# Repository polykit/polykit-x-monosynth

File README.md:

# Polykit X1 Semi Modular Synthesizer

This repository contains schematics, PCB layout files and front panel for an analog, semi modular, patchable synthesizer. It is an interface that works in conjunction with my voice card https://github.com/polykit/polykit-x-voice-card

Specs of the voice card:

* a VCO with saw, pulse and triangle signal
* an envelope generator
* a multimode filter with 8 different filter responses
* an external input
* and a panning stereo output

See voice card repository for a full feature list.

Specs of the semi modular interface:

* a LFO where the waveform can be blended between triangle and pulse signal
* a wave folder
* a two channel mixer where one input can be attenuated
* an additional attenuator
* a buffered multiple
* different offset voltages
* and a power supply
* 3D printable case

Video playlist on its functionality and design process: https://www.youtube.com/watch?v=2grRbG7IwDw&list=PLUKLEU8jmlbHH4_13YZM0MI6ez4gYQPfy

Gerber files [can be found here](plots/), front panel files are located [here](frontpanel).

## BOM

|Ref                                                                                                                                                      |Qnty|Value              |Name                  |Description                                                             |
|---------------------------------------------------------------------------------------------------------------------------------------------------------|----|-------------------|----------------------|------------------------------------------------------------------------|
|C1, C2                                                                                                                                                   |2   |1000uF             |C_Polarized           |Electrolytic capacitor                                                     |
|C3, C4                                                                                                                                                   |2   |100uF              |C_Polarized           |Electrolytic capacitor                                                     |
|C5, C6                                                                                                                                                   |2   |10uF               |C_Polarized           |Electrolytic capacitor                                                     |
|C7, C8                                                                                                                                                   |2   |1uF                |C_Polarized           |Electrolytic capacitor                                                     |
|C9                                                                                                                                                       |1   |2u2 non-polarized |C                     |Film or ceramic capacitor                                                   |
|C10, C11, C12, C13, C14                                                                                                                                  |5   |100n               |C                     |Ceramic capacitor                                                   |
|D1                                                                                                                                                       |1   |LED                |LED                   |Light emitting diode                                                    |
|D2, D3                                                                                                                                                   |2   |US1G               |US1G                  |400V, 1A, General Purpose Rectifier Diode, SMA(DO-214AC)                |
|D4, D6, D7, D8, D9, D10, D11, D12, D13, D14, D15                                                                                                         |11  |BAS85              |D_Schottky            |Schottky diode                                                          |
|D5                                                                                                                                                       |1   |Dual LED           |LED_Dual_Bidirectional|Dual LED, bidirectional                                                 |
|J1                                                                                                                                                       |1   |OUT LEFT           |AudioJack2_SwitchT    |Audio Jack, 2 Poles (Mono / TS), https://www.thonk.co.uk/shop/thonkiconn|
|J2                                                                                                                                                       |1   |OUT RIGHT          |AudioJack2_SwitchT    |Audio Jack, 2 Poles (Mono / TS), https://www.thonk.co.uk/shop/thonkiconn|
|J3                                                                                                                                                       |1   |ADSR_OUT           |AudioJack2_SwitchT    |Audio Jack, 2 Poles (Mono / TS), https://www.thonk.co.uk/shop/thonkiconn|
|J4                                                                                                                                                       |1   |GATE               |AudioJack2_SwitchT    |Audio Jack, 2 Poles (Mono / TS), https://www.thonk.co.uk/shop/thonkiconn|
|J5                                                                                                                                                       |1   |TRIGGER            |AudioJack2_SwitchT    |Audio Jack, 2 Poles (Mono / TS), https://www.thonk.co.uk/shop/thonkiconn|
|J6                                                                                                                                                       |1   |Conn_01x36         |Conn_01x36            |Pinheader, 01x36                                                        |
|J7                                                                                                                                                       |1   |12V AC             |Jack-DC               |Barrel Jack Socket, 12V AC/AC 1A wall wart power supply is needed              |
|J8                                                                                                                                                       |1   |LFO                |AudioJack2_SwitchT    |Audio Jack, 2 Poles (Mono / TS), https://www.thonk.co.uk/shop/thonkiconn|
|J9                                                                                                                                                       |1   |PAN_CV             |AudioJack2_SwitchT    |Audio Jack, 2 Poles (Mono / TS), https://www.thonk.co.uk/shop/thonkiconn|
|J10                                                                                                                                                      |1   |PWM CV             |AudioJack2_SwitchT    |Audio Jack, 2 Poles (Mono / TS), https://www.thonk.co.uk/shop/thonkiconn|
|J11                                                                                                                                                      |1   |RES CV             |AudioJack2_SwitchT    |Audio Jack, 2 Poles (Mono / TS), https://www.thonk.co.uk/shop/thonkiconn|
|J12                                                                                                                                                      |1   |FREQ CV            |AudioJack2_SwitchT    |Audio Jack, 2 Poles (Mono / TS), https://www.thonk.co.uk/shop/thonkiconn|
|J13                                                                                                                                                      |1   |PITCH CV 1V/OCT    |AudioJack2_SwitchT    |Audio Jack, 2 Poles (Mono / TS), https://www.thonk.co.uk/shop/thonkiconn|
|J14                                                                                                                                                      |1   |EXT IN             |AudioJack2_SwitchT    |Audio Jack, 2 Poles (Mono / TS), https://www.thonk.co.uk/shop/thonkiconn|
|J15                                                                                                                                                      |1   |VCA CV             |AudioJack2_SwitchT    |Audio Jack, 2 Poles (Mono / TS), https://www.thonk.co.uk/shop/thonkiconn|
|J16                                                                                                                                                      |1   |HARD SYNC          |AudioJack2_SwitchT    |Audio Jack, 2 Poles (Mono / TS), https://www.thonk.co.uk/shop/thonkiconn|
|J17                                                                                                                                                      |1   |SOFT SYNC          |AudioJack2_SwitchT    |Audio Jack, 2 Poles (Mono / TS), https://www.thonk.co.uk/shop/thonkiconn|
|J18                                                                                                                                                      |1   |FM                 |AudioJack2_SwitchT    |Audio Jack, 2 Poles (Mono / TS), https://www.thonk.co.uk/shop/thonkiconn|
|J19                                                                                                                                                      |1   |MULT               |AudioJack2_SwitchT    |Audio Jack, 2 Poles (Mono / TS), https://www.thonk.co.uk/shop/thonkiconn|
|J20                                                                                                                                                      |1   |WAVE IN            |AudioJack2_SwitchT    |Audio Jack, 2 Poles (Mono / TS), https://www.thonk.co.uk/shop/thonkiconn|
|J21                                                                                                                                                      |1   |ATT IN (+5V)       |AudioJack2_SwitchT    |Audio Jack, 2 Poles (Mono / TS), https://www.thonk.co.uk/shop/thonkiconn|
|J22                                                                                                                                                      |1   |MULT1              |AudioJack2_SwitchT    |Audio Jack, 2 Poles (Mono / TS), https://www.thonk.co.uk/shop/thonkiconn|
|J23                                                                                                                                                      |1   |MULT2              |AudioJack2_SwitchT    |Audio Jack, 2 Poles (Mono / TS), https://www.thonk.co.uk/shop/thonkiconn|
|J24                                                                                                                                                      |1   |ATT OUT            |AudioJack2_SwitchT    |Audio Jack, 2 Poles (Mono / TS), https://www.thonk.co.uk/shop/thonkiconn|
|J25                                                                                                                                                      |1   |MIX IN2            |                      |Can be used as default input for MIX2 when not patched                  |
|J26                                                                                                                                                      |1   |MIX IN1 (-5V)      |AudioJack2_SwitchT    |Audio Jack, 2 Poles (Mono / TS), https://www.thonk.co.uk/shop/thonkiconn|
|J27                                                                                                                                                      |1   |MIX IN2            |AudioJack2_SwitchT    |Audio Jack, 2 Poles (Mono / TS), https://www.thonk.co.uk/shop/thonkiconn|
|J28                                                                                                                                                      |1   |WAVE OUT           |AudioJack2_SwitchT    |Audio Jack, 2 Poles (Mono / TS), https://www.thonk.co.uk/shop/thonkiconn|
|J29                                                                                                                                                      |1   |MIX OUT            |AudioJack2_SwitchT    |Audio Jack, 2 Poles (Mono / TS), https://www.thonk.co.uk/shop/thonkiconn|
|Q1, Q3                                                                                                                                                   |2   |BC847              |BC847                 |0.1A Ic, 45V Vce, NPN Transistor, SOT-23                                |
|Q2                                                                                                                                                       |1   |BC857              |BC857                 |0.1A Ic, 45V Vce, PNP Transistor, SOT-23                                |
|R1, R18, R19, R47, R50                                                                                                                                   |5   |10k                |R                     |Resistor                                                                |
|R2, R3, R4, R5, R20, R21, R45, R46, R54, R58                                                                                                             |10  |1k                 |R                     |Resistor                                                                |
|R10                                                                                                                                                      |1   |100                |R                     |Resistor                                                                |
|R11, R12, R13, R15, R22, R23, R24, R25, R27, R28, R29, R30, R31, R32, R33, R34, R35, R36, R37, R38, R39, R40, R41, R43, R44, R51, R52, R53, R55, R56, R57|31  |100k               |R                     |Resistor                                                                |
|R14                                                                                                                                                      |1   |220k               |R                     |Resistor                                                                |
|R16                                                                                                                                                      |1   |15k                |R                     |Resistor                                                                |
|R17, R48, R49                                                                                                                                            |3   |12k                |R                     |Resistor                                                                |
|R26                                                                                                                                                      |1   |47k                |R                     |Resistor                                                                |
|R42                                                                                                                                                      |1   |470k               |R                     |Resistor                                                                |
|RV1                                                                                                                                                      |1   |B100k LEVEL1       |R_POT-Device          |Potentiometer RK097 Vertical                                            |
|RV2                                                                                                                                                      |1   |B100k LEVEL2       |R_POT-Device          |Potentiometer RK097 Vertical                                            |
|RV3                                                                                                                                                      |1   |10k LFO TRIM       |R_Potentiometer_Trim  |Trim-potentiometer                                                      |
|RV4                                                                                                                                                      |1   |B1M LFO RATE       |R_POT-Device          |Potentiometer RK097 Vertical                                            |
|RV5                                                                                                                                                      |1   |B100k LFO WAVE     |R_POT-Device          |Potentiometer RK097 Vertical                                            |
|RV6                                                                                                                                                      |1   |B100k PANNING      |R_POT-Device          |Potentiometer RK097 Vertical                                            |
|RV7                                                                                                                                                      |1   |B100k A            |R_POT-Device          |Potentiometer RK097 Vertical                                            |
|RV8                                                                                                                                                      |1   |B100k D            |R_POT-Device          |Potentiometer RK097 Vertical                                            |
|RV9                                                                                                                                                      |1   |B100k S            |R_POT-Device          |Potentiometer RK097 Vertical                                            |
|RV10                                                                                                                                                     |1   |B100k R            |R_POT-Device          |Potentiometer RK097 Vertical                                            |
|RV11                                                                                                                                                     |1   |B100k RES          |R_POT-Device          |Potentiometer RK097 Vertical                                            |
|RV12                                                                                                                                                     |1   |B100k FREQ         |R_POT-Device          |Potentiometer RK097 Vertical                                            |
|RV13                                                                                                                                                     |1   |B100k PWM          |R_POT-Device          |Potentiometer RK097 Vertical                                            |
|RV14                                                                                                                                                     |1   |B100k TUNE         |R_POT-Device          |Potentiometer RK097 Vertical                                            |
|RV15                                                                                                                                                     |1   |B100k ATT          |R_POT-Device          |Potentiometer RK097 Vertical                                            |
|RV16                                                                                                                                                     |1   |B100k MIX IN1 LEVEL|R_POT-Device          |Potentiometer RK097 Vertical                                            |
|SW1                                                                                                                                                      |1   |EXT_ON             |SW_SPDT               |Switch, single pole double throw                                        |
|SW2                                                                                                                                                      |1   |FILTER_A           |SW_SPDT               |Switch, single pole double throw                                        |
|SW3                                                                                                                                                      |1   |FILTER_B           |SW_SPDT               |Switch, single pole double throw                                        |
|SW4                                                                                                                                                      |1   |FILTER_C           |SW_SPDT               |Switch, single pole double throw                                        |
|SW5                                                                                                                                                      |1   |RES_MODE           |SW_SPDT_MSM           |Switch, single pole double throw, center OFF position                   |
|SW6                                                                                                                                                      |1   |FREQ_MODE          |SW_SPDT_MSM           |Switch, single pole double throw, center OFF position                   |
|SW7                                                                                                                                                      |1   |SAW_TRIANGLE       |SW_SPDT               |Switch, single pole double throw                                        |
|U1                                                                                                                                                       |1   |MC78M12_TO252      |78M12 TO-252          |Positive 500mA 35V Linear Regulator, Fixed Output 5V, TO-252 (D-PAK)    |
|U2                                                                                                                                                       |1   |MC79M12_TO252      |79M12 TO-252          |Negative 500mA 35V Linear Regulator, Fixed Output -12V, TO-252 (D-PAK)  |
|U3                                                                                                                                                       |1   |L78L05_SO8         |78L05 SO-8            |Positive 100mA 30V Linear Regulator, Fixed Output 5V, SO-8              |
|U4                                                                                                                                                       |1   |L79L05_SO8         |79L05 SO-8            |Negative 100mA -30V Linear Regulator, Fixed Output -5V, SO-8            |
|U5, U6, U7, U8                                                                                                                                           |4   |TL074              |TL074                 |Quad Low-Noise JFET-Input Operational Amplifiers, DIP-14/SOIC-14        |
|U9                                                                                                                                                       |1   |TL072              |TL072                 |Dual Low-Noise JFET-Input Operational Amplifiers, DIP-8/SOIC-8          |

## Tuning

See voice card repository for details on tuning. Additional male/female dupont cables are needed in order to get access to the trimpots. Minimal set of connections are ground, all four voltages, PITCH, PWM, ADSR_*, GATE, LVL2, FREQ_CV and outputs.

## Modifications

`SAW` output of the oscillator can be added to `MIX IN2` default input via a 1k resistor, eg. by tapping into the signal between `R1` and `U6` pin 8 on the voice card.

## References

Voice Card: https://github.com/polykit/polykit-x-voice-card

Footprints: https://github.com/polykit/kicad

Wavefolder: https://www.elby-designs.com/webtek/cgs/cgs52/cgs52_folder.html

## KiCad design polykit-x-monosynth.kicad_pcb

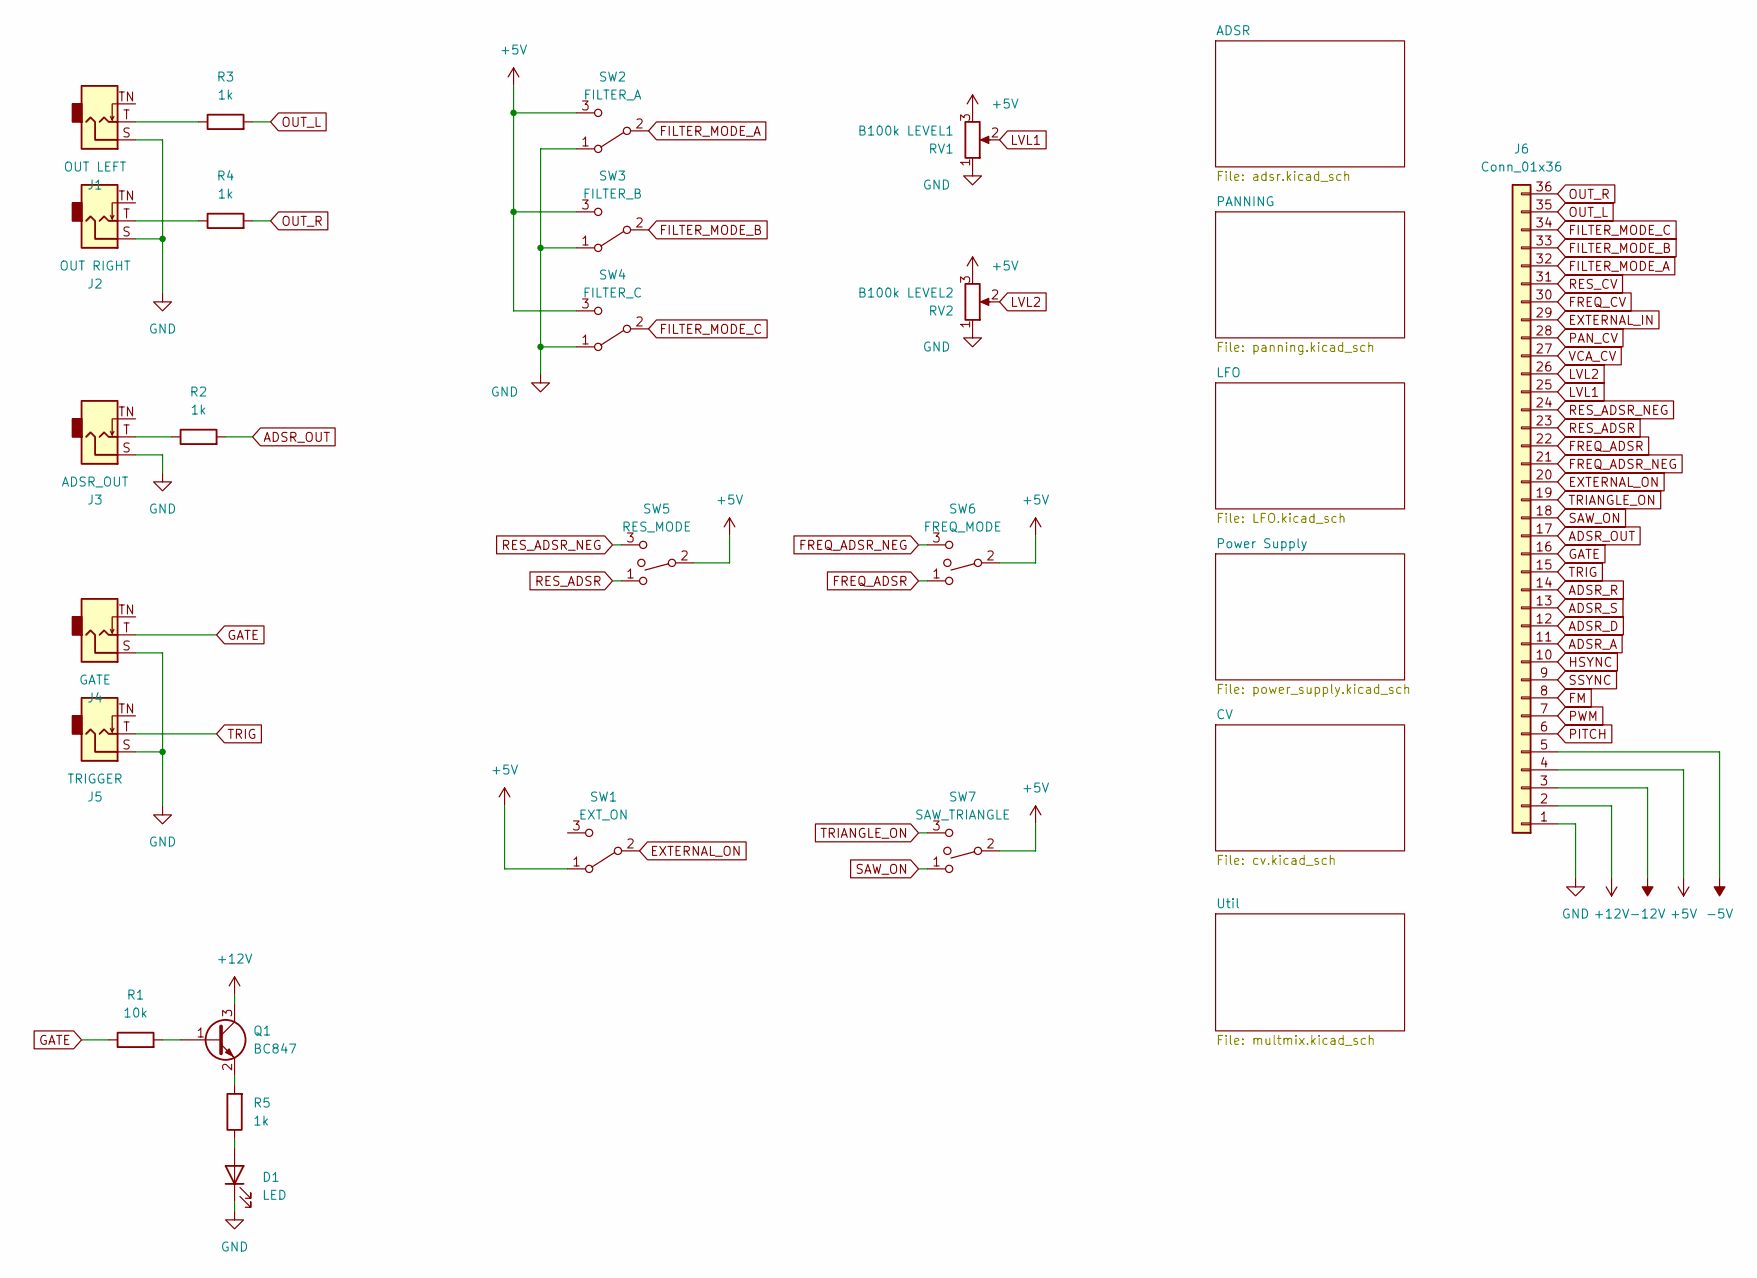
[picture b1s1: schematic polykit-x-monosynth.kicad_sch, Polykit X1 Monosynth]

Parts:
D1: LED; LED_D5.0mm
J1: OUT LEFT; Jack_3.5mm_QingPu_WQP-PJ398SM_Vertical_CircularHoles
J2: OUT RIGHT; Jack_3.5mm_QingPu_WQP-PJ398SM_Vertical_CircularHoles
J3: ADSR_OUT; Jack_3.5mm_QingPu_WQP-PJ398SM_Vertical_CircularHoles
J4: GATE; Jack_3.5mm_QingPu_WQP-PJ398SM_Vertical_CircularHoles
J5: TRIGGER; Jack_3.5mm_QingPu_WQP-PJ398SM_Vertical_CircularHoles
J6: Conn_01x36; PinSocket_1x36_P2.54mm_Vertical
Q1: BC847; SOT-23; LCSC C8659
R1: 10k; R_1206_3216Metric_Pad1.30x1.75mm_HandSolder; LCSC C17902
R2, R3, R4, R5: 1k; R_1206_3216Metric_Pad1.30x1.75mm_HandSolder; LCSC C4410
RV1: B100k LEVEL1; Potentiometer_Alpha_RD901F-40-00D_Single_Vertical_CircularH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
RV2: B100k LEVEL2; Potentiometer_Alpha_RD901F-40-00D_Single_Vertical_CircularH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
SW1: EXT_ON; switch-spdt
SW2: FILTER_A; switch-spdt
SW3: FILTER_B; switch-spdt
SW4: FILTER_C; switch-spdt
SW5: RES_MODE; switch-spdt
SW6: FREQ_MODE; switch-spdt
SW7: SAW_TRIANGLE; switch-spdt

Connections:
+5V: J6.4, RV1.3, RV2.3, SW1.1 (A), SW2.3 (C), SW3.3 (C), SW4.3 (C), SW5.2, SW6.2, SW7.2; also elsewhere on the board
+12V: J6.2, Q1.3 (C); also elsewhere on the board
-5V: J6.5; also elsewhere on the board
-12V: J6.3; also elsewhere on the board
ADSR_A: J6.11; also elsewhere on the board
ADSR_D: J6.12; also elsewhere on the board
ADSR_OUT: J6.17, R2.2; also elsewhere on the board
ADSR_R: J6.14; also elsewhere on the board
ADSR_S: J6.13; also elsewhere on the board
EXTERNAL_IN: J6.29; also elsewhere on the board
EXTERNAL_ON: J6.20, SW1.2 (B)
FILTER_MODE_A: J6.32, SW2.2 (B)
FILTER_MODE_B: J6.33, SW3.2 (B)
FILTER_MODE_C: J6.34, SW4.2 (B)
FM: J6.8; also elsewhere on the board
FREQ_ADSR: J6.22, SW6.1
FREQ_ADSR_NEG: J6.21, SW6.3
FREQ_CV: J6.30; also elsewhere on the board
GATE: J4.T, J6.16, R1.1
HSYNC: J6.10; also elsewhere on the board
LVL1: J6.25, RV1.2
LVL2: J6.26, RV2.2
unnamed: D1.2 (A), R5.1
unnamed: J1.T, R3.1
unnamed: J2.T, R4.1
unnamed: J3.T, R2.1
unnamed: Q1.1 (B), R1.2
unnamed: Q1.2 (E), R5.2
OUT_L: J6.35, R3.2
OUT_R: J6.36, R4.2
PAN_CV: J6.28; also elsewhere on the board
PITCH: J6.6; also elsewhere on the board
PWM: J6.7; also elsewhere on the board
RES_ADSR: J6.23, SW5.1
RES_ADSR_NEG: J6.24, SW5.3
RES_CV: J6.31; also elsewhere on the board
SAW_ON: J6.18, SW7.1
SSYNC: J6.9; also elsewhere on the board
TRIANGLE_ON: J6.19, SW7.3
TRIG: J5.T, J6.15
VCA_CV: J6.27; also elsewhere on the board

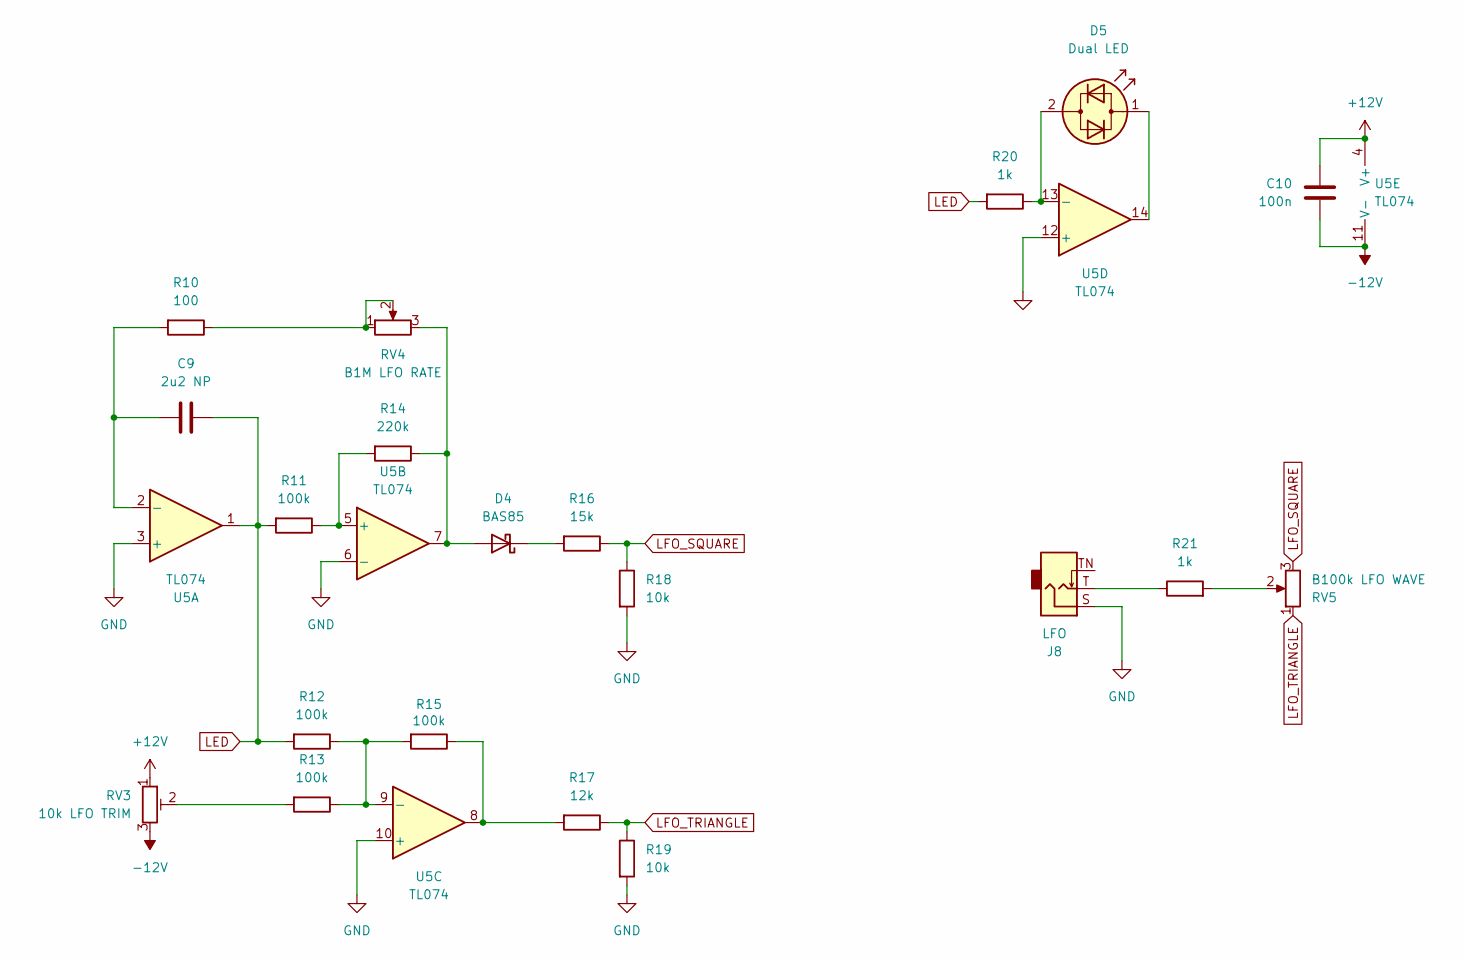
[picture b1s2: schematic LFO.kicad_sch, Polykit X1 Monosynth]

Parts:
C9: 2u2 NP; C_1206_3216Metric_Pad1.33x1.80mm_HandSolder; LCSC C134236
C10: 100n; C_1206_3216Metric_Pad1.33x1.80mm_HandSolder; LCSC C24497
D4: BAS85; D_MiniMELF; LCSC C46677
D5: Dual LED; LED_D5.0mm
J8: LFO; Jack_3.5mm_QingPu_WQP-PJ398SM_Vertical_CircularHoles
R10: 100; R_1206_3216Metric_Pad1.30x1.75mm_HandSolder; LCSC C17901
R11, R12, R13, R15: 100k; R_1206_3216Metric_Pad1.30x1.75mm_HandSolder; LCSC C17900
R14: 220k; R_1206_3216Metric_Pad1.30x1.75mm_HandSolder; LCSC C17956
R16: 15k; R_1206_3216Metric_Pad1.30x1.75mm_HandSolder; LCSC C17912
R17: 12k; R_1206_3216Metric_Pad1.30x1.75mm_HandSolder; LCSC C17912
R18, R19: 10k; R_1206_3216Metric_Pad1.30x1.75mm_HandSolder; LCSC C17902
R20, R21: 1k; R_1206_3216Metric_Pad1.30x1.75mm_HandSolder; LCSC C4410
RV3: 10k LFO TRIM; Potentiometer_Bourns_3314J_Vertical; LCSC C36376
RV4: B1M LFO RATE; Potentiometer_Alpha_RD901F-40-00D_Single_Vertical_CircularH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
RV5: B100k LFO WAVE; Potentiometer_Alpha_RD901F-40-00D_Single_Vertical_CircularH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
U5: TL074; SO-14_3.9x8.65mm_P1.27mm; LCSC C6963

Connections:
+12V: C10.1, RV3.1, U5.4 (V+); also elsewhere on the board
-12V: C10.2, RV3.3, U5.11 (V-); also elsewhere on the board
LED: C9.1, R11.2, R12.2, R20.2, U5.1
LFO_SQUARE: R16.1, R18.1, RV5.3
LFO_TRIANGLE: R17.1, R19.1, RV5.1
unnamed: C9.2, R10.2, U5.2 (-)
unnamed: D4.1 (K), R16.2
unnamed: D4.2 (A), R14.1, RV4.3, U5.7
unnamed: D5.1 (KA), U5.14
unnamed: D5.2 (AK), R20.1, U5.13 (-)
unnamed: J8.T, R21.1
unnamed: R10.1, RV4.1, RV4.2
unnamed: R11.1, R14.2, U5.5 (+)
unnamed: R12.1, R13.1, R15.2, U5.9 (-)
unnamed: R13.2, RV3.2
unnamed: R15.1, R17.2, U5.8
unnamed: R21.2, RV5.2

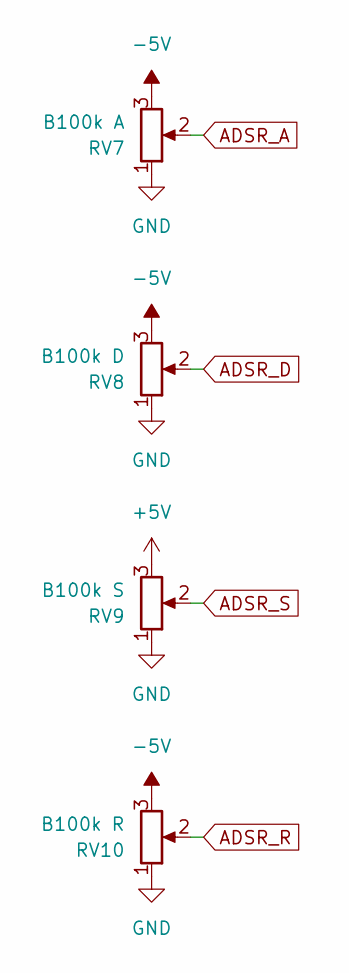
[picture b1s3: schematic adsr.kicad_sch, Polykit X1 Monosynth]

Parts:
RV7: B100k A; Potentiometer_Alpha_RD901F-40-00D_Single_Vertical_CircularH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
RV8: B100k D; Potentiometer_Alpha_RD901F-40-00D_Single_Vertical_CircularH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
RV9: B100k S; Potentiometer_Alpha_RD901F-40-00D_Single_Vertical_CircularH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
RV10: B100k R; Potentiometer_Alpha_RD901F-40-00D_Single_Vertical_CircularH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

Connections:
+5V: RV9.3; also elsewhere on the board
-5V: RV7.3, RV8.3, RV10.3; also elsewhere on the board
ADSR_A: RV7.2; also elsewhere on the board
ADSR_D: RV8.2; also elsewhere on the board
ADSR_R: RV10.2; also elsewhere on the board
ADSR_S: RV9.2; also elsewhere on the board

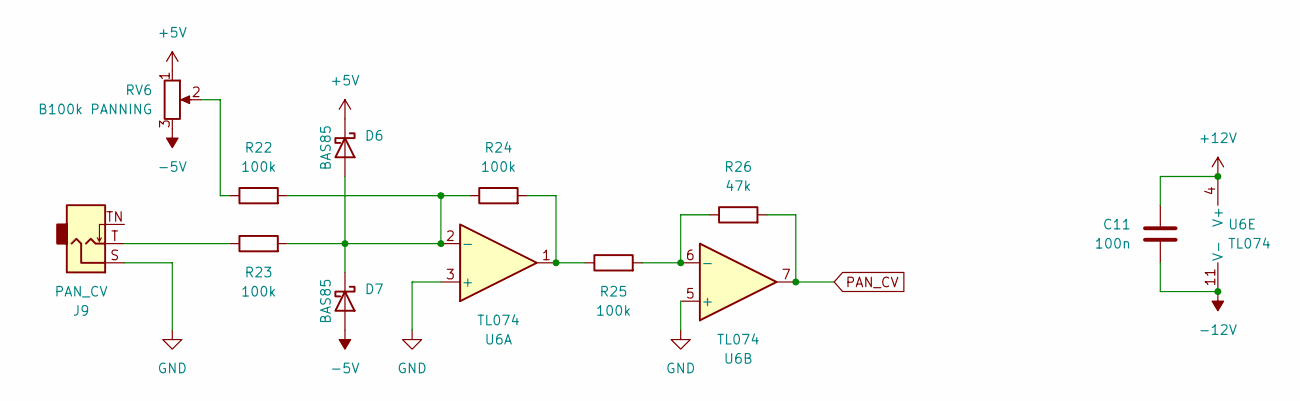
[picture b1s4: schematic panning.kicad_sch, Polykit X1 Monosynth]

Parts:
C11: 100n; C_1206_3216Metric_Pad1.33x1.80mm_HandSolder; LCSC C24497
D6, D7: BAS85; D_MiniMELF; LCSC C46677
J9: PAN_CV; Jack_3.5mm_QingPu_WQP-PJ398SM_Vertical_CircularHoles
R22, R23, R24, R25: 100k; R_1206_3216Metric_Pad1.30x1.75mm_HandSolder; LCSC C17900
R26: 47k; R_1206_3216Metric_Pad1.30x1.75mm_HandSolder; LCSC C25833
RV6: B100k PANNING; Potentiometer_Alpha_RD901F-40-00D_Single_Vertical_CircularH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
U6: TL074; SO-14_3.9x8.65mm_P1.27mm; LCSC C6963

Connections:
+5V: D6.1 (K), RV6.1; also elsewhere on the board
+12V: C11.1, U6.4 (V+); also elsewhere on the board
-5V: D7.2 (A), RV6.3; also elsewhere on the board
-12V: C11.2, U6.11 (V-); also elsewhere on the board
unnamed: D6.2 (A), D7.1 (K), R22.2, R23.2, R24.1, U6.2 (-)
unnamed: J9.T, R23.1
unnamed: R22.1, RV6.2
unnamed: R24.2, R25.1, U6.1
unnamed: R25.2, R26.1, U6.6 (-)
PAN_CV: R26.2, U6.7; also elsewhere on the board

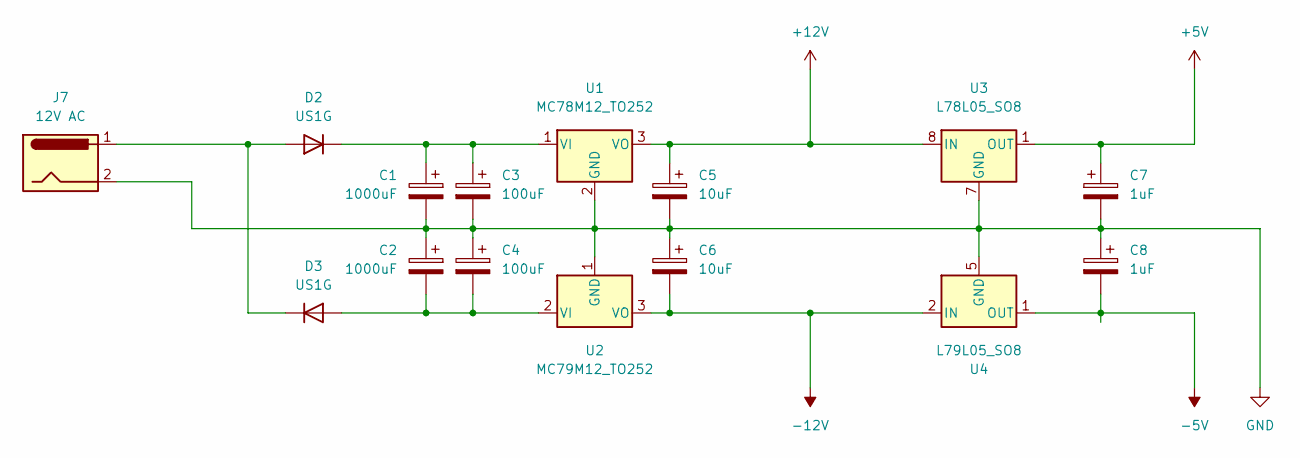
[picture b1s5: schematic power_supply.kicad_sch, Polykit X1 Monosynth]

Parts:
C1, C2: 1000uF; CP_Elec_10x10; LCSC C2904877*
C3, C4: 100uF; CP_Elec_6.3x7.7; LCSC C125975
C5, C6: 10uF; CP_Elec_4x5.8; LCSC C134237*
C7, C8: 1uF; CP_Elec_4x5.4; LCSC C445065
D2, D3: US1G; D_SMA
J7: 12V AC; BarrelJack_Horizontal
U1: MC78M12_TO252; TO-252-2; LCSC C67851
U2: MC79M12_TO252; TO-252-2; LCSC C154823
U3: L78L05_SO8; SOIC-8_3.9x4.9mm_P1.27mm; LCSC C7372
U4: L79L05_SO8; SOIC-8_3.9x4.9mm_P1.27mm; LCSC C222122

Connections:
+5V: C7.1, U3.1 (OUT); also elsewhere on the board
+12V: C5.1, U1.3 (VO), U3.8 (IN); also elsewhere on the board
-5V: C8.2, U4.1 (OUT); also elsewhere on the board
-12V: C6.2, U2.3 (VO), U4.2 (IN), U4.3 (IN), U4.6 (IN), U4.7 (IN); also elsewhere on the board
unnamed: C1.1, C3.1, D2.1 (K), U1.1 (VI)
unnamed: C2.2, C4.2, D3.2 (A), U2.2 (VI)
unnamed: D2.2 (A), D3.1 (K), J7.1

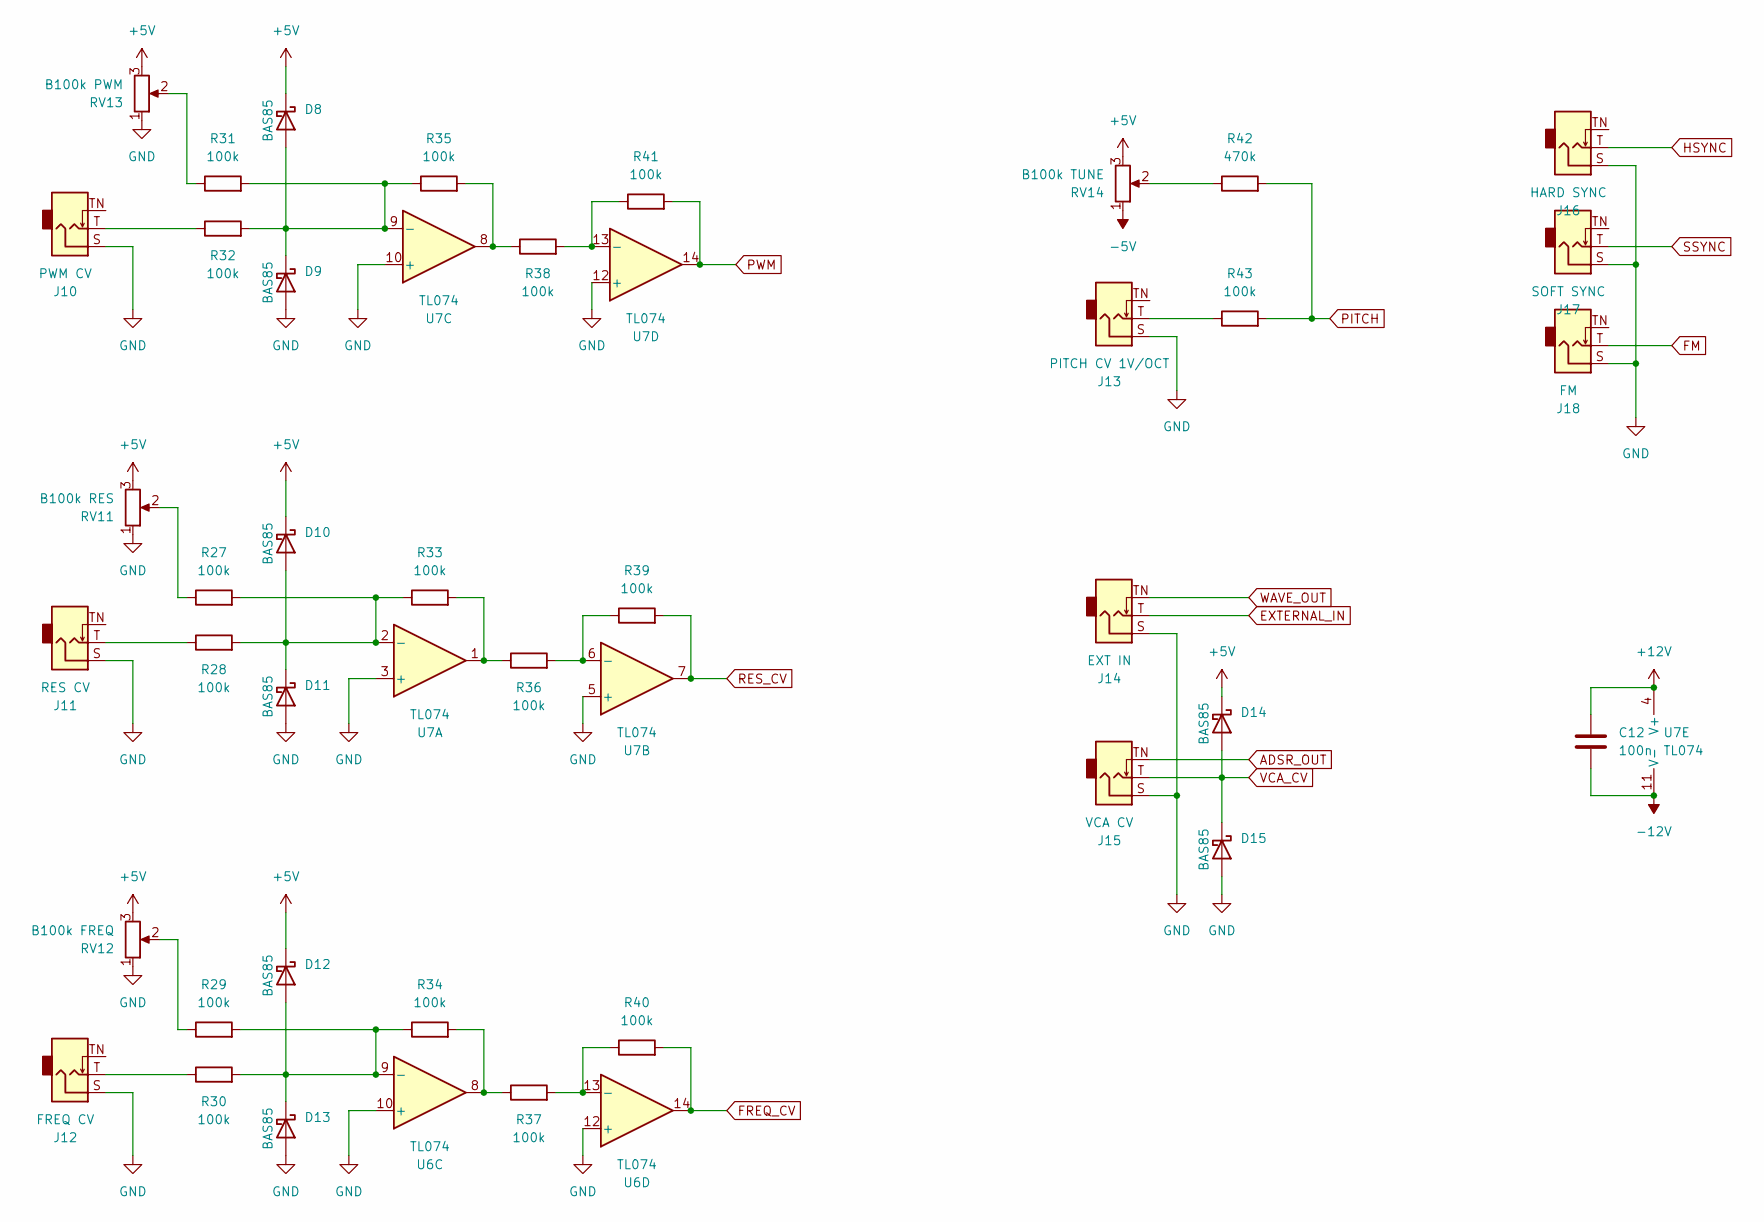
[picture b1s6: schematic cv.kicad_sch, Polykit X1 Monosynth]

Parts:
C12: 100n; C_1206_3216Metric_Pad1.33x1.80mm_HandSolder; LCSC C24497
D8, D9, D10, D11, D12, D13, D14, D15: BAS85; D_MiniMELF; LCSC C46677
J10: PWM CV; Jack_3.5mm_QingPu_WQP-PJ398SM_Vertical_CircularHoles
J11: RES CV; Jack_3.5mm_QingPu_WQP-PJ398SM_Vertical_CircularHoles
J12: FREQ CV; Jack_3.5mm_QingPu_WQP-PJ398SM_Vertical_CircularHoles
J13: PITCH CV 1V/OCT; Jack_3.5mm_QingPu_WQP-PJ398SM_Vertical_CircularHoles
J14: EXT IN; Jack_3.5mm_QingPu_WQP-PJ398SM_Vertical_CircularHoles
J15: VCA CV; Jack_3.5mm_QingPu_WQP-PJ398SM_Vertical_CircularHoles
J16: HARD SYNC; Jack_3.5mm_QingPu_WQP-PJ398SM_Vertical_CircularHoles
J17: SOFT SYNC; Jack_3.5mm_QingPu_WQP-PJ398SM_Vertical_CircularHoles
J18: FM; Jack_3.5mm_QingPu_WQP-PJ398SM_Vertical_CircularHoles
R27, R28, R29, R30, R31, R32, R33, R34, R35, R36, R37, R38, R39, R40, R41, R43: 100k; R_1206_3216Metric_Pad1.30x1.75mm_HandSolder; LCSC C17900
R42: 470k; R_1206_3216Metric_Pad1.30x1.75mm_HandSolder; LCSC C25663
RV11: B100k RES; Potentiometer_Alpha_RD901F-40-00D_Single_Vertical_CircularH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
RV12: B100k FREQ; Potentiometer_Alpha_RD901F-40-00D_Single_Vertical_CircularH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
RV13: B100k PWM; Potentiometer_Alpha_RD901F-40-00D_Single_Vertical_CircularH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
RV14: B100k TUNE; Potentiometer_Alpha_RD901F-40-00D_Single_Vertical_CircularH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
U6, U7: TL074; SO-14_3.9x8.65mm_P1.27mm; LCSC C6963

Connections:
+5V: D8.1 (K), D10.1 (K), D12.1 (K), D14.1 (K), RV11.3, RV12.3, RV13.3, RV14.3; also elsewhere on the board
+12V: C12.1, U7.4 (V+); also elsewhere on the board
-5V: RV14.1; also elsewhere on the board
-12V: C12.2, U7.11 (V-); also elsewhere on the board
ADSR_OUT: J15.TN; also elsewhere on the board
EXTERNAL_IN: J14.T; also elsewhere on the board
FM: J18.T; also elsewhere on the board
FREQ_CV: R40.2, U6.14; also elsewhere on the board
HSYNC: J16.T; also elsewhere on the board
unnamed: D8.2 (A), D9.1 (K), R31.2, R32.2, R35.1, U7.9 (-)
unnamed: D10.2 (A), D11.1 (K), R27.2, R28.2, R33.1, U7.2 (-)
unnamed: D12.2 (A), D13.1 (K), R29.2, R30.2, R34.1, U6.9 (-)
unnamed: J10.T, R32.1
unnamed: J11.T, R28.1
unnamed: J12.T, R30.1
unnamed: J13.T, R43.1
unnamed: R27.1, RV11.2
unnamed: R29.1, RV12.2
unnamed: R31.1, RV13.2
unnamed: R33.2, R36.1, U7.1
unnamed: R34.2, R37.1, U6.8
unnamed: R35.2, R38.1, U7.8
unnamed: R36.2, R39.1, U7.6 (-)
unnamed: R37.2, R40.1, U6.13 (-)
unnamed: R38.2, R41.1, U7.13 (-)
unnamed: R42.1, RV14.2
PITCH: R42.2, R43.2; also elsewhere on the board
PWM: R41.2, U7.14; also elsewhere on the board
RES_CV: R39.2, U7.7; also elsewhere on the board
SSYNC: J17.T; also elsewhere on the board
VCA_CV: D14.2 (A), D15.1 (K), J15.T; also elsewhere on the board
WAVE_OUT: J14.TN; also elsewhere on the board

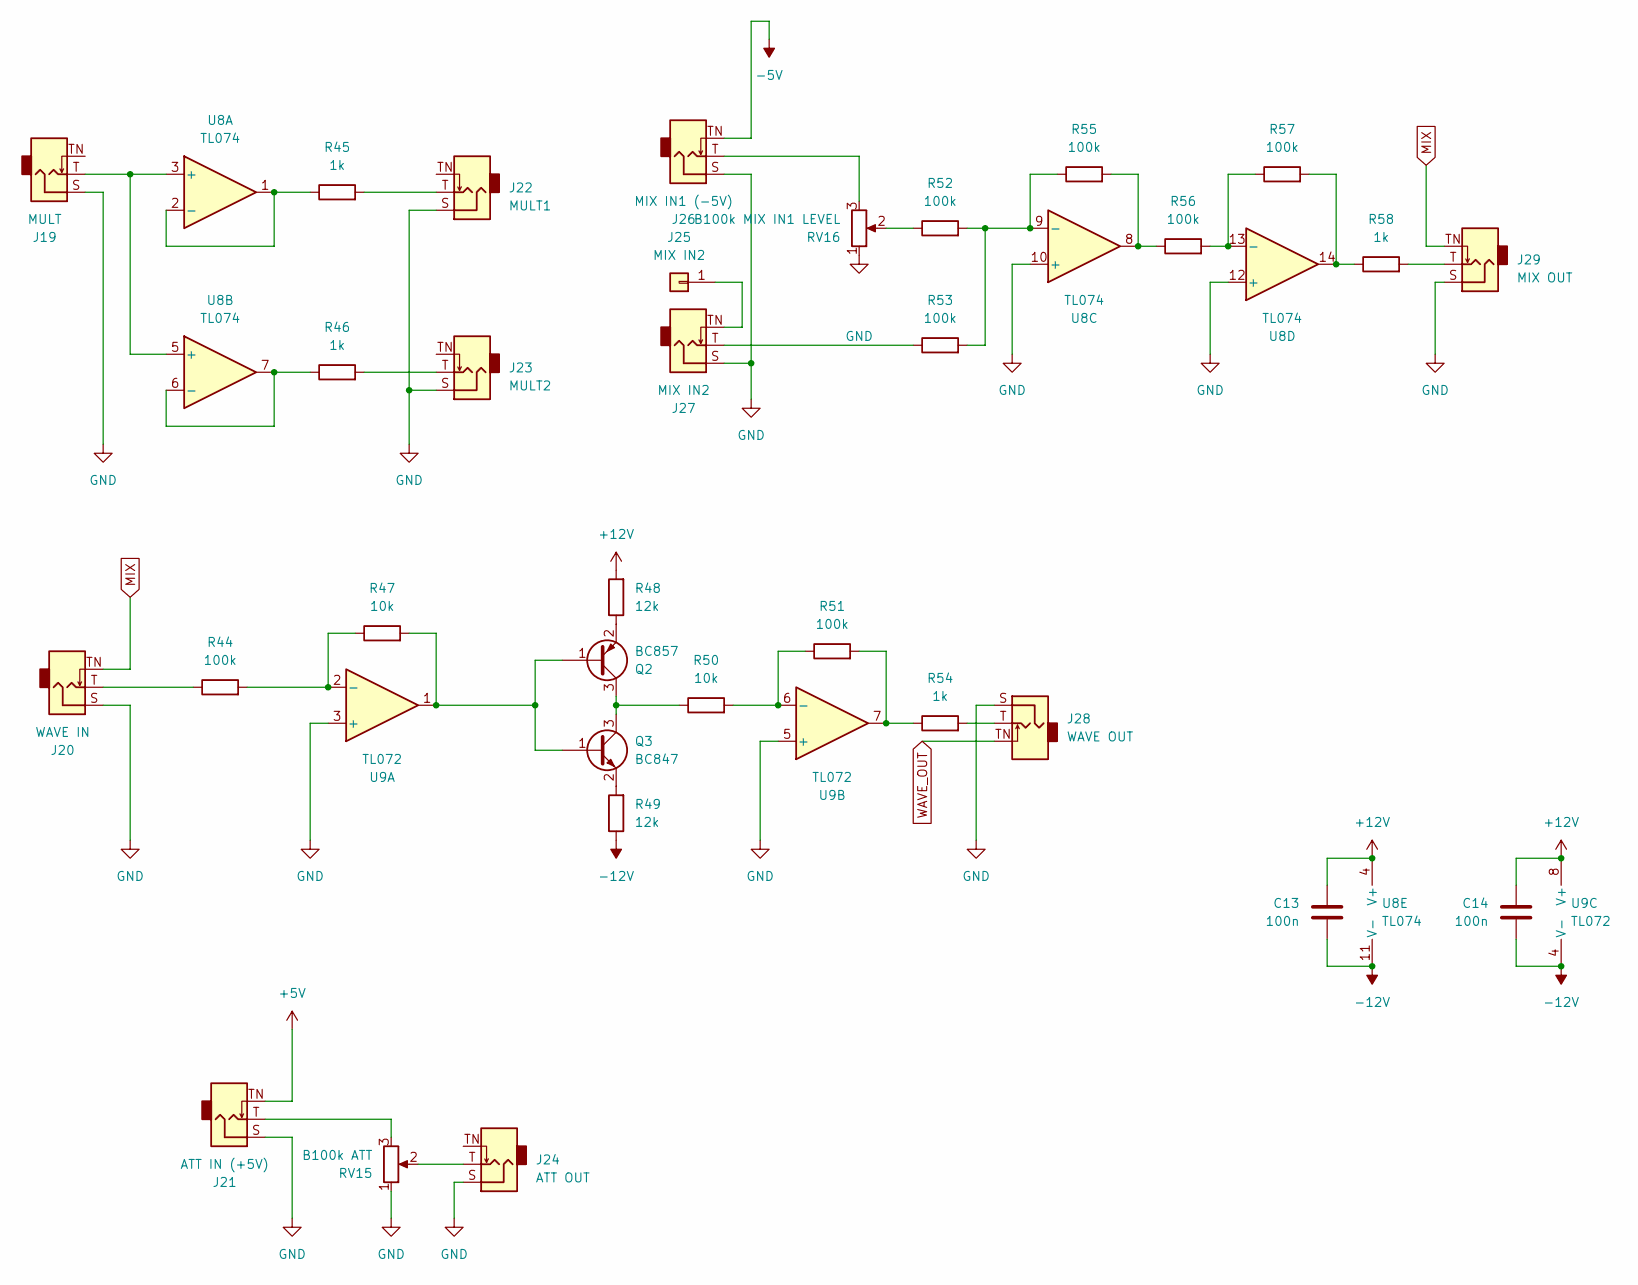
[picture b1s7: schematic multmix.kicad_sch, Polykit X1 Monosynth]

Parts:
C13, C14: 100n; C_1206_3216Metric_Pad1.33x1.80mm_HandSolder; LCSC C24497
J19: MULT; Jack_3.5mm_QingPu_WQP-PJ398SM_Vertical_CircularHoles
J20: WAVE IN; Jack_3.5mm_QingPu_WQP-PJ398SM_Vertical_CircularHoles
J21: ATT IN (+5V); Jack_3.5mm_QingPu_WQP-PJ398SM_Vertical_CircularHoles
J22: MULT1; Jack_3.5mm_QingPu_WQP-PJ398SM_Vertical_CircularHoles
J23: MULT2; Jack_3.5mm_QingPu_WQP-PJ398SM_Vertical_CircularHoles
J24: ATT OUT; Jack_3.5mm_QingPu_WQP-PJ398SM_Vertical_CircularHoles
J25: MIX IN2; Pin_D1.0mm_L10.0mm
J26: MIX IN1 (-5V); Jack_3.5mm_QingPu_WQP-PJ398SM_Vertical_CircularHoles
J27: MIX IN2; Jack_3.5mm_QingPu_WQP-PJ398SM_Vertical_CircularHoles
J28: WAVE OUT; Jack_3.5mm_QingPu_WQP-PJ398SM_Vertical_CircularHoles
J29: MIX OUT; Jack_3.5mm_QingPu_WQP-PJ398SM_Vertical_CircularHoles
Q2: BC857; SOT-23
Q3: BC847; SOT-23
R44, R51: 100k; R_1206_3216Metric_Pad1.30x1.75mm_HandSolder; LCSC C4410
R45, R46, R54, R58: 1k; R_1206_3216Metric_Pad1.30x1.75mm_HandSolder; LCSC C4410
R47, R50: 10k; R_1206_3216Metric_Pad1.30x1.75mm_HandSolder; LCSC C4410
R48, R49: 12k; R_1206_3216Metric_Pad1.30x1.75mm_HandSolder; LCSC C4410
R52, R53, R55, R56, R57: 100k; R_1206_3216Metric_Pad1.30x1.75mm_HandSolder; LCSC C17900
RV15: B100k ATT; Potentiometer_Alpha_RD901F-40-00D_Single_Vertical_CircularH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
RV16: B100k MIX IN1 LEVEL; Potentiometer_Alpha_RD901F-40-00D_Single_Vertical_CircularH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
U8: TL074; SO-14_3.9x8.65mm_P1.27mm; LCSC C6963
U9: TL072

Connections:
+5V: J21.TN; also elsewhere on the board
+12V: C13.1, C14.1, R48.2, U8.4 (V+), U9.8 (V+); also elsewhere on the board
-5V: J26.TN; also elsewhere on the board
-12V: C13.2, C14.2, R49.1, U8.11 (V-), U9.4 (V-); also elsewhere on the board
MIX: J20.TN, J29.TN
unnamed: J19.T, U8.3 (+), U8.5 (+)
unnamed: J20.T, R44.1
unnamed: J21.T, RV15.3
unnamed: J22.T, R45.2
unnamed: J23.T, R46.2
unnamed: J24.T, RV15.2
unnamed: J25.1, J27.TN
unnamed: J26.T, RV16.3
unnamed: J27.T, R53.1
unnamed: J28.T, R54.2
unnamed: J29.T, R58.2
unnamed: Q2.1 (B), Q3.1 (B), R47.2, U9.1
unnamed: Q2.2 (E), R48.1
unnamed: Q2.3 (C), Q3.3 (C), R50.1
unnamed: Q3.2 (E), R49.2
unnamed: R44.2, R47.1, U9.2 (-)
unnamed: R45.1, U8.1, U8.2 (-)
unnamed: R46.1, U8.6 (-), U8.7
unnamed: R50.2, R51.1, U9.6 (-)
unnamed: R51.2, R54.1, U9.7
unnamed: R52.1, RV16.2
unnamed: R52.2, R53.2, R55.1, U8.9 (-)
unnamed: R55.2, R56.1, U8.8
unnamed: R56.2, R57.1, U8.13 (-)
unnamed: R57.2, R58.1, U8.14
WAVE_OUT: J28.TN; also elsewhere on the board

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
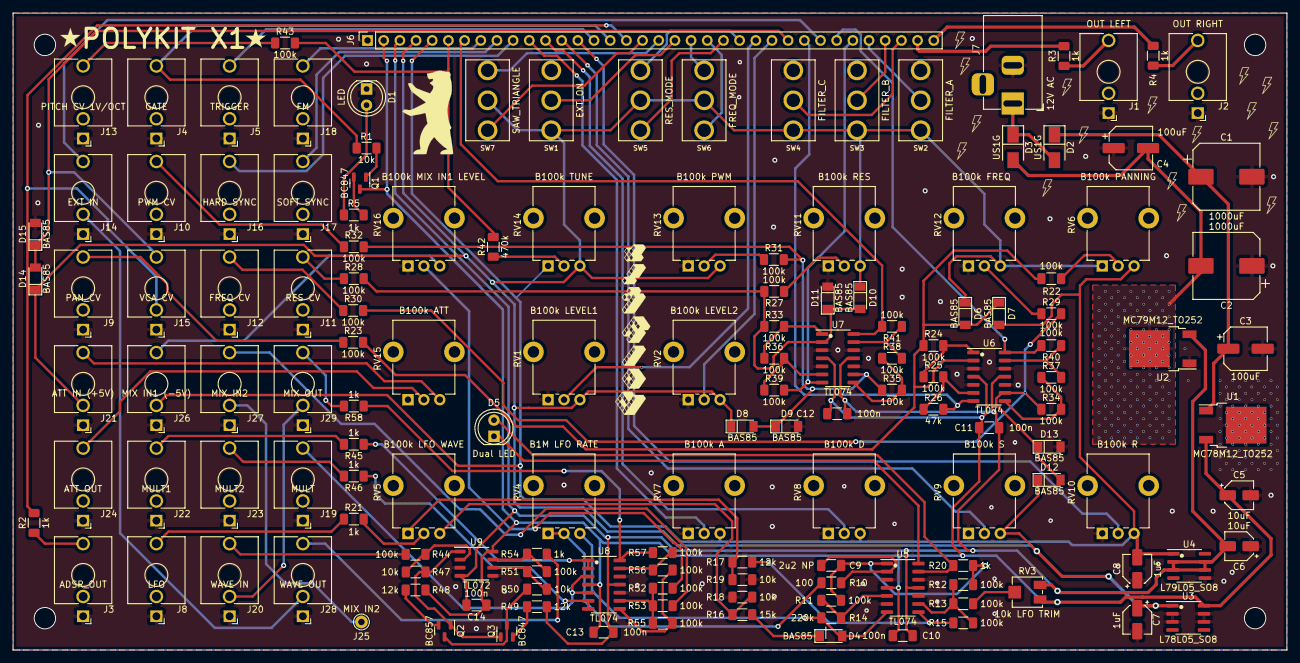
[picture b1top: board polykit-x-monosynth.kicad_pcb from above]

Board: 2 copper layers, 200.0 x 100.0 mm, 147 parts (0 on the bottom side), 109 nets.

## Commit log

2022-10-18 Initial import
2022-11-22 Fix power supply, add schematics pdf
2022-11-22 Fix date
2022-12-17 Add bom to readme
2023-03-01 Update case 3d model
2023-12-24 Add readme modifications and footprint
